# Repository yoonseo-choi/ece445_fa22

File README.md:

# ECE 445 Fall 2022 - Team 23

**Team Members**
- Yoonseo Choi (yschoi4)
- Aaron Gros (aygros2)
- Sean Kim (sk5)

**Lateral Movement Force-Feedback VR Gloves**

We have created a low-cost and open source force-feedback VR glove for lateral finger movement. It is able to acurate track and restrict the index, middle, ring, and pinky finger.

**Google Drive Repository** 
[Google Repo Link](https://drive.google.com/drive/folders/11H3rUvDkAtsJpdgwuR88esnsnRXGqsm2?usp=sharing)

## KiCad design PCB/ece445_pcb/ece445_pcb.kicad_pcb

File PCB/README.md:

# PCB 

**PCB Design for VR Glove**

This branch contains all files and folders related tothe pcb layout and design of the VR glove.

**Basic Git Commands**

1. git checkout pcb ; for switching into pcb branch

2. git pull ; get updated version of remote repo

3a. git add {whatever file you want to add} ; adds specific files

3b. git add . ; this adds all the changes you made

4. git commit -m "{whatever message}"

5. git push ; to update the remote repo

git status ; to check status of branch

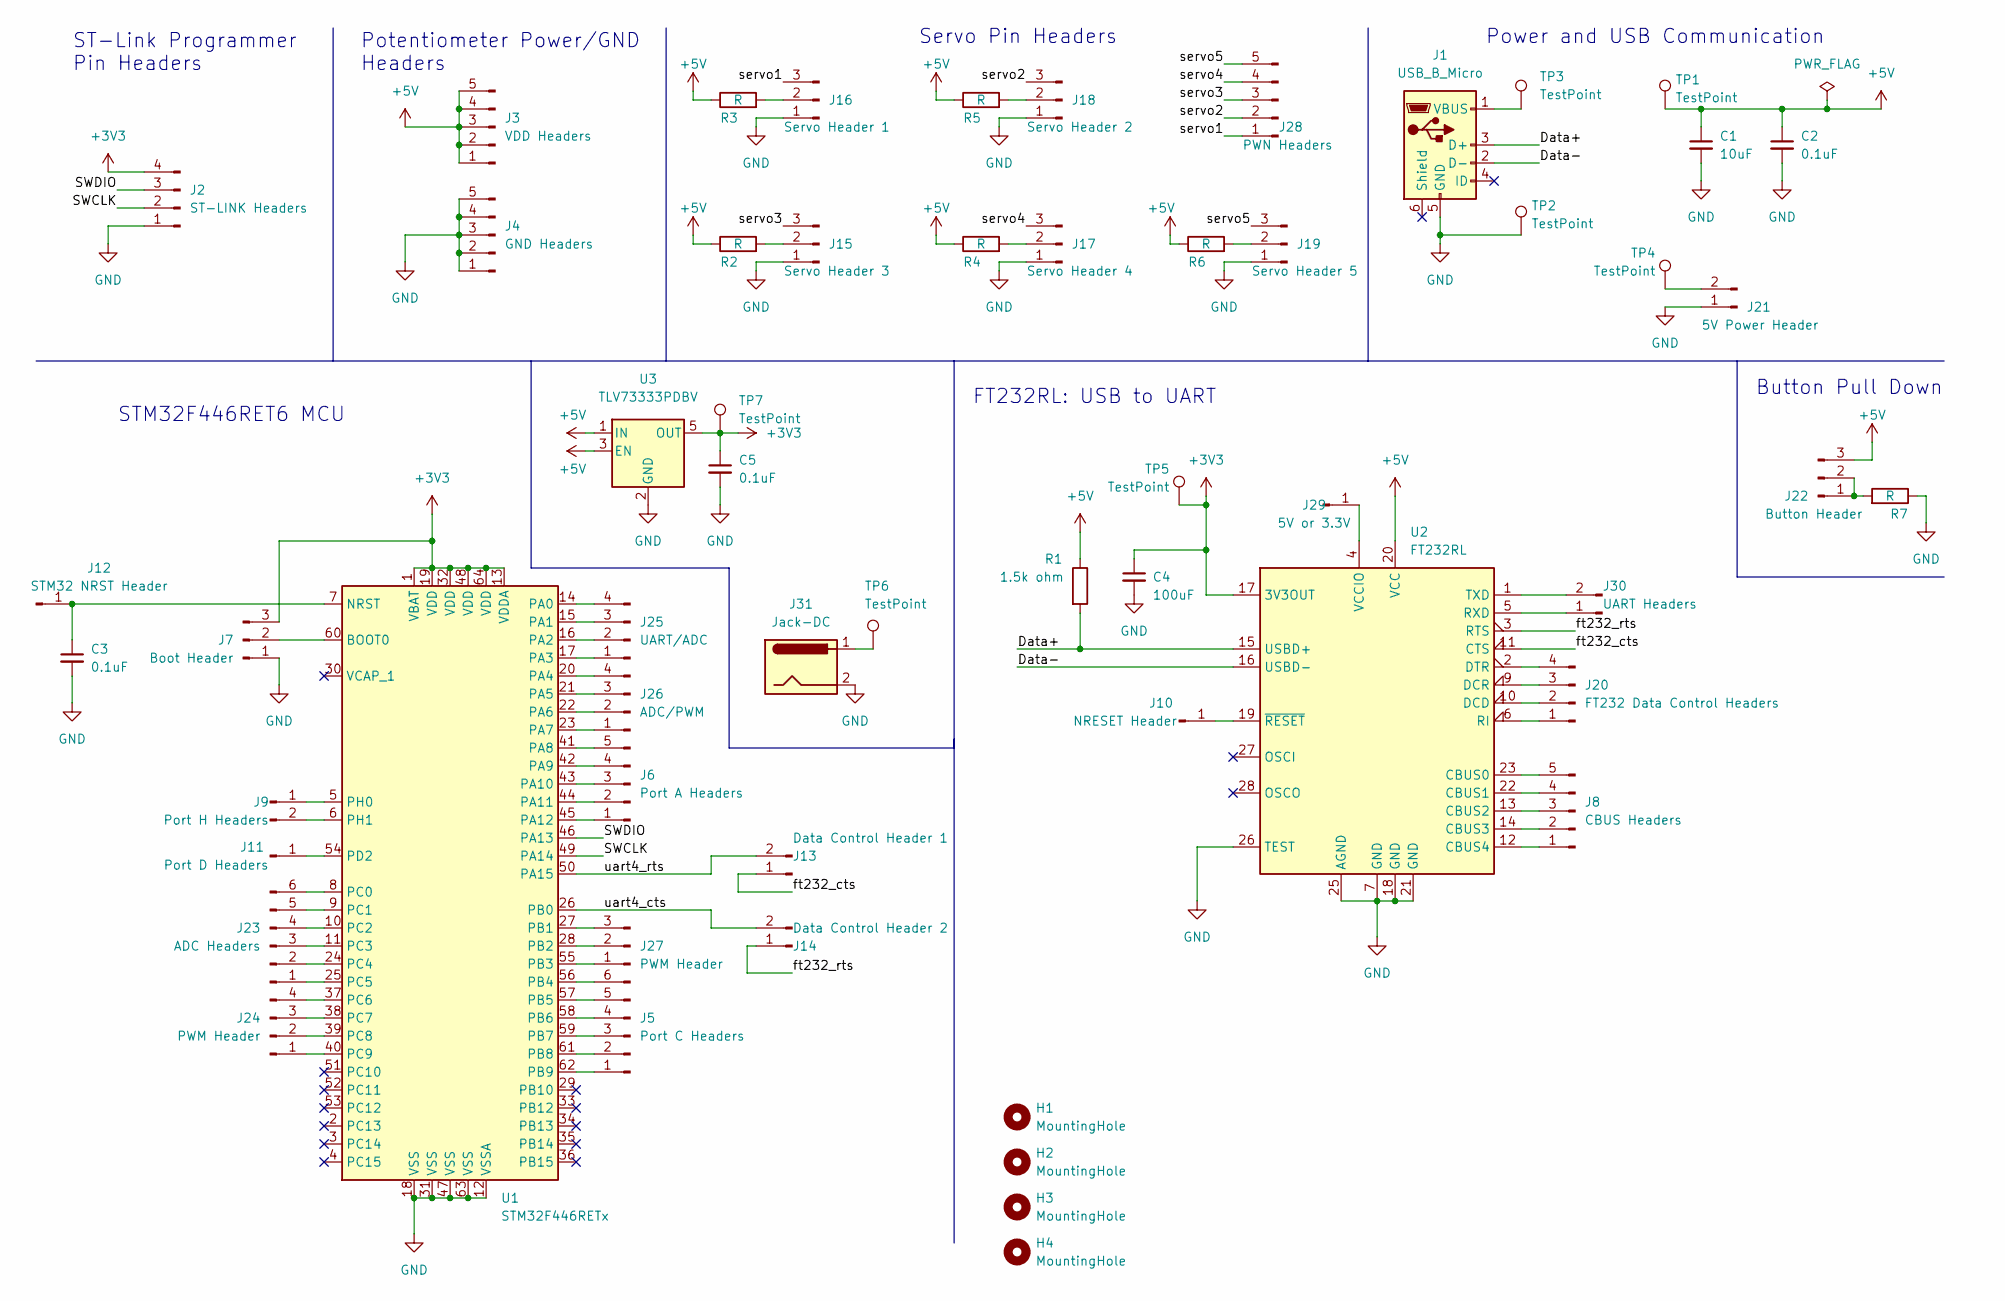
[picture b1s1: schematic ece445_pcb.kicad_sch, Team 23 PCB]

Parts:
C1: 10uF; C_0805_2012Metric_Pad1.18x1.45mm_HandSolder
C2, C3, C5: 0.1uF; C_0805_2012Metric_Pad1.18x1.45mm_HandSolder
C4: 100uF; C_0805_2012Metric_Pad1.18x1.45mm_HandSolder
H1, H2, H3, H4: MountingHole; MountingHole_3.2mm_M3
J1: USB_B_Micro; USB_Micro-B_Molex-105133-0031
J2: ST-LINK Headers; PinHeader_1x04_P2.54mm_Vertical
J3: VDD Headers; PinHeader_1x05_P2.54mm_Vertical
J4: GND Headers; PinHeader_1x05_P2.54mm_Vertical
J5: Port C Headers; PinHeader_1x06_P2.54mm_Vertical
J6: Port A Headers; PinHeader_1x05_P2.54mm_Vertical
J7: Boot Header; PinHeader_1x03_P2.54mm_Vertical
J8: CBUS Headers; PinHeader_1x05_P2.54mm_Vertical
J9: Port H Headers; PinHeader_1x02_P2.54mm_Vertical
J10: NRESET Header; PinHeader_1x01_P2.54mm_Vertical
J11: Port D Headers; PinHeader_1x01_P2.54mm_Vertical
J12: STM32 NRST Header; PinHeader_1x01_P2.54mm_Vertical
J13: Data Control Header 1; PinHeader_1x02_P2.54mm_Vertical
J14: Data Control Header 2; PinHeader_1x02_P2.54mm_Vertical
J15: Servo Header 3; PinHeader_1x03_P2.54mm_Vertical
J16: Servo Header 1; PinHeader_1x03_P2.54mm_Vertical
J17: Servo Header 4; PinHeader_1x03_P2.54mm_Vertical
J18: Servo Header 2; PinHeader_1x03_P2.54mm_Vertical
J19: Servo Header 5; PinHeader_1x03_P2.54mm_Vertical
J20: FT232 Data Control Headers; PinHeader_1x04_P2.54mm_Vertical
J21: 5V Power Header; PinHeader_1x02_P2.54mm_Vertical
J22: Button Header; PinHeader_1x03_P2.54mm_Vertical
J23: ADC Headers; PinHeader_1x06_P2.54mm_Vertical
J24: PWM Header; PinHeader_1x04_P2.54mm_Vertical
J25: UART/ADC; PinHeader_1x04_P2.54mm_Vertical
J26: ADC/PWM; PinHeader_1x04_P2.54mm_Vertical
J27: PWM Header; PinHeader_1x03_P2.54mm_Vertical
J28: PWN Headers; PinHeader_1x05_P2.54mm_Vertical
J29: 5V or 3.3V; PinHeader_1x01_P2.54mm_Vertical
J30: UART Headers; PinHeader_1x02_P2.54mm_Vertical
J31: Jack-DC; BarrelJack_Wuerth_6941xx301002
R1: 1.5k ohm; R_0805_2012Metric_Pad1.20x1.40mm_HandSolder
R2, R3, R4, R5, R6, R7: R; R_Axial_DIN0207_L6.3mm_D2.5mm_P5.08mm_Vertical
TP1, TP2, TP3, TP4, TP5, TP6, TP7: TestPoint; TestPoint_Keystone_5019_Minature
U1: STM32F446RETx; LQFP-64_10x10mm_P0.5mm
U2: FT232RL; SSOP-28_5.3x10.2mm_P0.65mm
U3: TLV73333PDBV; SOT-23-5

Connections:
+3V3: C4.1, C5.1, J2.4, J7.3, TP5.1, TP7.1, U1.1 (VBAT), U1.13 (VDDA), U1.19 (VDD), U1.32 (VDD), U1.48 (VDD), U1.64 (VDD), U2.17 (3V3OUT), U3.5 (OUT)
+5V: C1.1, C2.1, J3.1, J3.2, J3.3, J3.4, J3.5, J22.3, R1.1, R2.1, R3.1, R4.1, R5.1, R6.1, TP1.1, U2.20 (VCC), U3.1 (IN), U3.3 (EN)
/Data+: J1.3 (D+), R1.2, U2.15 (USBD+)
/Data-: J1.2 (D-), U2.16 (USBD-)
/SWCLK: J2.2, U1.49 (PA14)
/SWDIO: J2.3, U1.46 (PA13)
/ft232_cts: J13.1, U2.11 (CTS)
/ft232_rts: J14.1, U2.3 (RTS)
/servo1: J16.3, J28.1
/servo2: J18.3, J28.2
/servo3: J15.3, J28.3
/servo4: J17.3, J28.4
/servo5: J19.3, J28.5
/uart4_cts: J14.2, U1.26 (PB0)
/uart4_rts: J13.2, U1.50 (PA15)
GND: C1.2, C2.2, C3.2, C4.2, C5.2, J1.5 (GND), J2.1, J4.1, J4.2, J4.3, J4.4, J4.5, J7.1, J15.1, J16.1, J17.1, J18.1, J19.1, J21.1, J31.2, R7.1, TP2.1, U1.12 (VSSA), U1.18 (VSS), U1.31 (VSS), U1.47 (VSS), U1.63 (VSS), U2.7 (GND), U2.18 (GND), U2.21 (GND), U2.25 (AGND), U2.26 (TEST), U3.2 (GND)
unnamed: C3.1, J12.1, U1.7 (NRST)
unnamed: J1.1 (VBUS), TP3.1
unnamed: J5.1, U1.62 (PB9)
unnamed: J5.2, U1.61 (PB8)
unnamed: J5.3, U1.59 (PB7)
unnamed: J5.4, U1.58 (PB6)
unnamed: J5.5, U1.57 (PB5)
unnamed: J5.6, U1.56 (PB4)
unnamed: J6.1, U1.45 (PA12)
unnamed: J6.2, U1.44 (PA11)
unnamed: J6.3, U1.43 (PA10)
unnamed: J6.4, U1.42 (PA9)
unnamed: J6.5, U1.41 (PA8)
unnamed: J7.2, U1.60 (BOOT0)
unnamed: J8.1, U2.12 (CBUS4)
unnamed: J8.2, U2.14 (CBUS3)
unnamed: J8.3, U2.13 (CBUS2)
unnamed: J8.4, U2.22 (CBUS1)
unnamed: J8.5, U2.23 (CBUS0)
unnamed: J9.1, U1.5 (PH0)
unnamed: J9.2, U1.6 (PH1)
unnamed: J10.1, U2.19 (~RESET)
unnamed: J11.1, U1.54 (PD2)
unnamed: J15.2, R2.2
unnamed: J16.2, R3.2
unnamed: J17.2, R4.2
unnamed: J18.2, R5.2
unnamed: J19.2, R6.2
unnamed: J20.1, U2.6 (RI)
unnamed: J20.2, U2.10 (DCD)
unnamed: J20.3, U2.9 (DCR)
unnamed: J20.4, U2.2 (DTR)
unnamed: J21.2, TP4.1
unnamed: J22.1, J22.2, R7.2
unnamed: J23.1, U1.25 (PC5)
unnamed: J23.2, U1.24 (PC4)
unnamed: J23.3, U1.11 (PC3)
unnamed: J23.4, U1.10 (PC2)
unnamed: J23.5, U1.9 (PC1)
unnamed: J23.6, U1.8 (PC0)
unnamed: J24.1, U1.40 (PC9)
unnamed: J24.2, U1.39 (PC8)
unnamed: J24.3, U1.38 (PC7)
unnamed: J24.4, U1.37 (PC6)
unnamed: J25.1, U1.17 (PA3)
unnamed: J25.2, U1.16 (PA2)
unnamed: J25.3, U1.15 (PA1)
unnamed: J25.4, U1.14 (PA0)
unnamed: J26.1, U1.23 (PA7)
unnamed: J26.2, U1.22 (PA6)
unnamed: J26.3, U1.21 (PA5)
unnamed: J26.4, U1.20 (PA4)
unnamed: J27.1, U1.55 (PB3)
unnamed: J27.2, U1.28 (PB2)
unnamed: J27.3, U1.27 (PB1)
unnamed: J29.1, U2.4 (VCCIO)
unnamed: J30.1, U2.5 (RXD)
unnamed: J30.2, U2.1 (TXD)
unnamed: J31.1, TP6.1

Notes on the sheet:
FT232RL: USB to UART
Servo Pin Headers
Button Pull Down
Potentiometer Power/GND Headers
ST-Link Programmer Pin Headers
Power and USB Communication
STM32F446RET6 MCU

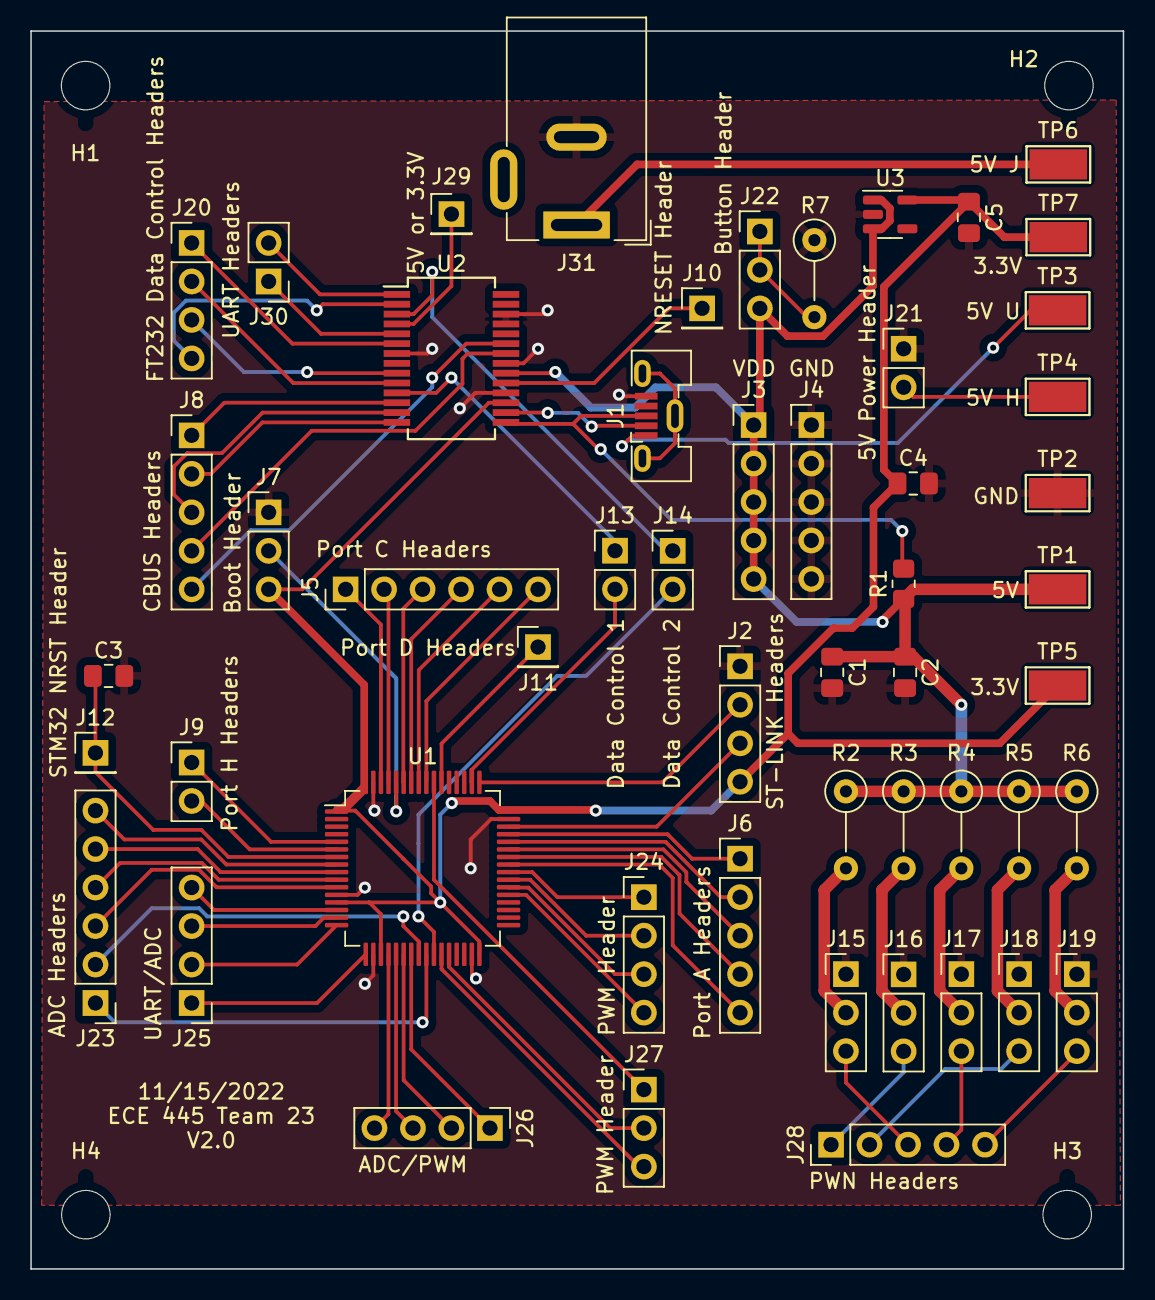
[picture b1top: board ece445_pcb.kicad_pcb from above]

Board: 2 copper layers, 72.1 x 81.7 mm, 57 parts (0 on the bottom side), 75 nets.

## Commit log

2022-09-19 update readme with images
2022-09-19 added project description
2022-09-22 added google drive repo to readme
2022-09-27 updated yoonseo notebook
2022-09-30 update yoonseo notebook
2022-10-09 update notebook for october 8th
2022-10-09 add notes to ft232
2022-12-07 updated electronic notebook with work log
2022-12-07 add datasheet to servo datasheet
2022-12-07 updated notebook from worklog up to 11/13
2022-12-07 updated notebook with final entries from worklog
2022-12-08 adding images for notebook
2022-12-08 adding image
2022-12-08 changed the file size
2022-12-08 more image
2022-12-08 picture size
2022-12-09 Update README.md
    notebook update
2022-12-09 Added readme images
2022-12-09 Updated notebook
2022-12-09 uploaded mechanical design
2022-12-09 Uploaded Software
2022-12-09 remove unnecesary file (is in google drive)
2022-12-09 uploaded images
2022-12-09 updated images
2022-12-09 updated description
2022-12-09 Uploaded the PCB files
2022-12-09 Uploaded firmware
2022-12-09 uploaded most recent unreal content files
